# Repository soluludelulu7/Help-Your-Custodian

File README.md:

# Help Your Custodian
Description:

- I have noticed that school trashcans often seem to stink a bit and it is probably due to wet waste not being taken out at the right time.
- Also, our custodians are too busy to peep inside every single one.
- Spending a moment of our life clicking a button to help our custodians out is the best way to help the community and make schools stink lesser.
- Help Your Custodian assists them by displaying the moisture level of a trashcan on an LED Matrix when students click a button while throwing away their trash.
- This helps avoid smelly trash can helping  keep schools clean and smell free.

PCB 3D View:

Bill of Materials (everything will be bought by me:

| Part                | Qty | Source          | Link                        | Cost   |
|---------------------|-----|-----------------|-----------------------------|--------|
| XIAO ESP32 C3       | 1   | Amazon          | https://a.co/d/0e2cZeYc     | $9.90  |
| MAX7219 Matrix      | 1   | Amazon          | https://a.co/d/0ffXBsqx     | $8.99  |
| Cherry MX Switch    | 1   | I have it       | none                        | none   |
| DHT11 Module        | 1   | Amazon          | https://a.co/d/0dia7duY     | $9.97  |
| Header Connectors   | 1   | Amazon          | https://a.co/d/083PV2Bl     | $7.99  |
| PCB                 | 5   | JLCPCB          | JLCPCB                      | $2.10  |

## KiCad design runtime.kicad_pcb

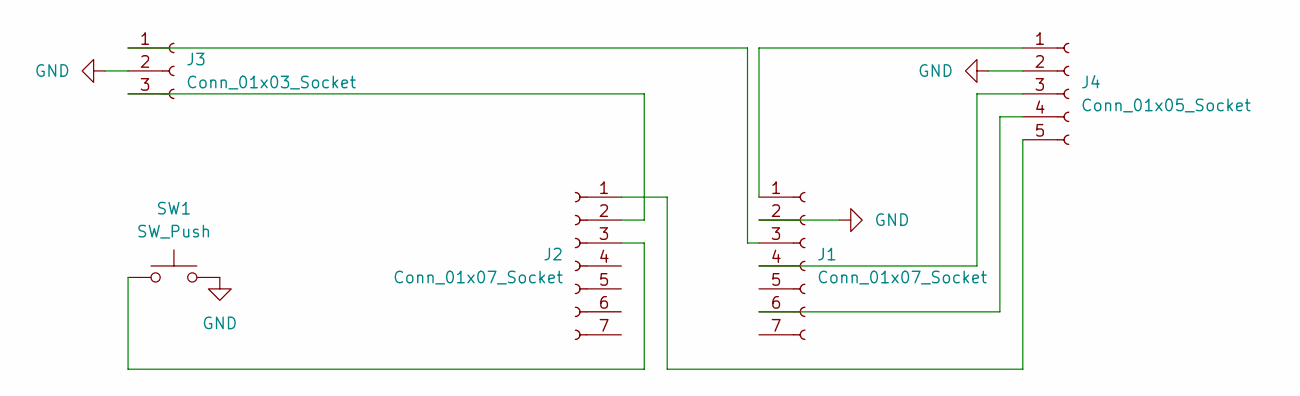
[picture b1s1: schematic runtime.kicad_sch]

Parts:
J1, J2: Conn_01x07_Socket; PinSocket_1x07_P2.54mm_Vertical
J3: Conn_01x03_Socket; PinSocket_1x03_P2.54mm_Vertical
J4: Conn_01x05_Socket; PinSocket_1x05_P2.54mm_Vertical
SW1: SW_Push; SW_Cherry_MX_1.00u_PCB

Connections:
GND: J1.2, J3.2, J4.2, SW1.2
unnamed: J1.1, J4.1
unnamed: J1.3, J3.1
unnamed: J1.4, J4.3
unnamed: J1.6, J4.4
unnamed: J2.1, J4.5
unnamed: J2.2, J3.3
unnamed: J2.3, SW1.1

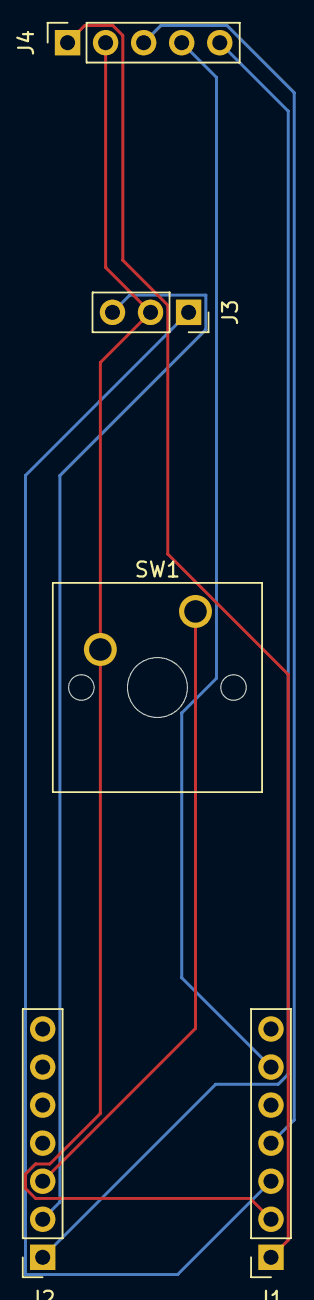
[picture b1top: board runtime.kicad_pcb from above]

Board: 2 copper layers, 5 parts (0 on the bottom side), 8 nets.
